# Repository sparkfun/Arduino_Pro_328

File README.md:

Arduino Pro 328
========================================

[*Arduino Pro 328 (DEV-10914)*](https://www.sparkfun.com/products/10914)

Arduino Pro does not come with connectors populated so that you can solder in any connector or wire with any orientation you need. 
We recommend first time Arduino users start with the Uno R3. It’s a great board that will get you up and running quickly. 
The Arduino Pro series is meant for users that understand the limitations of system voltage, lack of connectors, and USB off board.

Repository Contents
-------------------

* **/Hardware** - Eagle design files (.brd, .sch)
* **/Production** - Production panel files (.brd)

Documentation
--------------
* **[SparkFun Fritzing repo](https://github.com/sparkfun/Fritzing_Parts)** - Fritzing diagrams for SparkFun products.
* **[SparkFun 3D Model repo](https://github.com/sparkfun/3D_Models)** - 3D models of SparkFun products. 

Product Versions
----------------
* [3.3V/8MHz: DEV-10914](https://www.sparkfun.com/products/10914)- 3.3V/8MHz version of the Arduino Pro. 
* [5V/16MHz: DEV-10915] (https://www.sparkfun.com/products/10915)- 5V/16MHz version of the Arduino Pro. 

Revision History
----------------
Changes to v14 (date code: 8-24-11)
* updated library to increase annular ring size on all thru-hole pads (including package change on buzzer PTH)
* reposition 6x1 serial header to no longer overhang board
* BOM CHANGE - changes smd slide switch to stronger package with side mount tabs

Changes to v15 (date code: 9-21-11)
* changed package on the Buzzer to not include silk

Changes to v16 (date code: 12-20-11)
* Added OSHW logo

Changes to v17
* Added juicy silk graphics

Changes to v18
* Widened hard-to-read silk text

License Information
-------------------

This product is _**open source**_! 

Please review the LICENSE.md file for license information. 

If you have any questions or concerns on licensing, please contact techsupport@sparkfun.com.

Distributed as-is; no warranty is given.

- Your friends at SparkFun.

_**Note:** A portion of this sale is given back to Arduino LLC to help fund continued development of new tools and new IDE features._

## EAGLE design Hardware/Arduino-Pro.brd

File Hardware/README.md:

Arduino Pro Design Files
=====================================

The .sch and .brd files hare are Eagle CAD schematic and PCB design files from SparkFun Electronics.
A freeware version of Eagle can be found [here](http://www.cadsoftusa.com/download-eagle/freeware/).

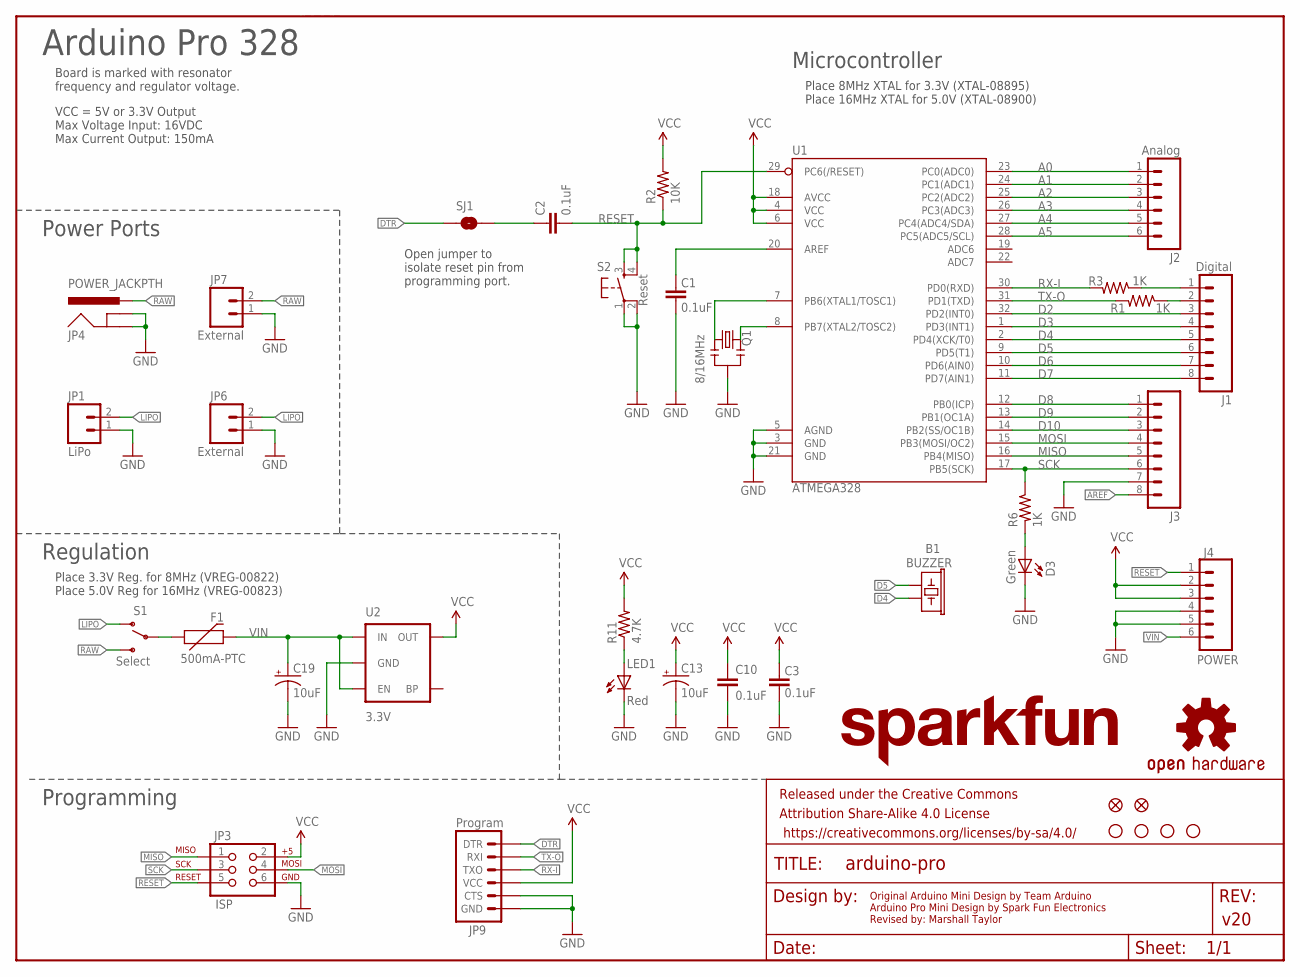
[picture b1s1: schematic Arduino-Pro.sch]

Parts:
B1: BUZZER; BUZZER-12MM-NS-KIT
C1, C2, C3, C10: 0.1uF; 0402-CAP
C13, C19: 10uF; EIA3216
D3: Green; LED-0603
F1: 500mA-PTC; PTC-1206
FRAME2: FRAME-LETTER; CREATIVE_COMMONS
J1: Digital; 1X08
J2: Analog; 1X06
J3: M081X08; 1X08
J4: POWER; 1X06
JP1: LiPo; JST-2-SMD
JP2, JP5: FIDUCIAL1X2.5; FIDUCIAL-1X2.5
JP3: ISP; 2X3
JP4: POWER_JACKPTH; POWER_JACK_PTH
JP6, JP7: External; 1X02
JP9: Program; 1X06-SMD
LED1: Red; LED-0603
Q1: 8/16MHz; RESONATOR-SMD
R1, R3, R6: 1K; 0402-RES
R2: 10K; 0402-RES
R11: 4.7K; 0402-RES
S1: Select; SWITCH-SPST-SMD-A
S2: Reset; TACTILE_SWITCH_SMD
SJ1: SOLDERJUMPERNC3; SJ_2S-NOTRACE
U1: ATMEGA328; TQFP32-08
U2: 3.3V; SOT23-5
U$1, U$3, U$9, U$10: STAND-OFF

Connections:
A0: J2.1, U1.23 (PC0(ADC0))
A1: J2.2, U1.24 (PC1(ADC1))
A2: J2.3, U1.25 (PC2(ADC2))
A3: J2.4, U1.26 (PC3(ADC3))
A4: J2.5, U1.27 (PC4(ADC4/SDA))
A5: J2.6, U1.28 (PC5(ADC5/SCL))
AREF: C1.2, J3.8, U1.20 (AREF)
D2: J1.3, U1.32 (PD2(INT0))
D3: J1.4, U1.1 (PD3(INT1))
D4: B1.- (2), J1.5, U1.2 (PD4(XCK/T0))
D5: B1.+ (1), J1.6, U1.9 (PD5(T1))
D6: J1.7, U1.10 (PD6(AIN0))
D7: J1.8, U1.11 (PD7(AIN1))
D8: J3.1, U1.12 (PB0(ICP))
D9: J3.2, U1.13 (PB1(OC1A))
D10: J3.3, U1.14 (PB2(SS/OC1B))
DTR: JP9.1 (DTR), SJ1.1
GND: C1.1, C3.1, C10.2, C13.C (-), C19.C (-), D3.C, J3.7, J4.4, J4.5, JP1.1, JP3.6, JP4.GND, JP4.GNDBREAK, JP6.1, JP7.1, JP9.5 (CTS), JP9.6 (GND), LED1.C, Q1.2, S2.1, S2.2, U1.3 (GND), U1.5 (AGND), U1.21 (GND), U2.2 (GND)
LIPO: JP1.2, JP6.2, S1.1 (O)
MISO: J3.5, JP3.1, U1.16 (PB4(MISO))
MOSI: J3.4, JP3.4, U1.15 (PB3(MOSI/OC2))
unnamed: C2.1, SJ1.2
unnamed: Q1.1, U1.8 (PB7(XTAL2/TOSC2))
unnamed: Q1.3, U1.7 (PB6(XTAL1/TOSC1))
unnamed: D3.A, R6.2
unnamed: F1.1, S1.2
unnamed: LED1.A, R11.1
RAW: JP4.PWR, JP7.2, S1.3 (S)
RESET: C2.2, J4.1, JP3.5, R2.1, S2.3, S2.4, U1.29 (PC6(/RESET))
RX-I: JP9.3 (TXO), R3.2, U1.30 (PD0(RXD))
RX-IP: J1.2, R1.1
SCK: J3.6, JP3.3, R6.1, U1.17 (PB5(SCK))
TX-O: JP9.2 (RXI), R1.2, U1.31 (PD1(TXD))
TX-OP: J1.1, R3.1
VCC: C3.2, C10.1, C13.A (+), J4.2, J4.3, JP3.2, JP9.4 (VCC), R2.2, R11.2, U1.4 (VCC), U1.6 (VCC), U1.18 (AVCC), U2.5 (OUT)
VIN: C19.A (+), F1.2, J4.6, U2.1 (IN), U2.3 (EN)

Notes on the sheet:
VCC = 5V or 3.3V Output Max Voltage Input: 16VDC Max Current Output: 150mA
Board is marked with resonator frequency and regulator voltage.
v20
Original Arduino Mini Design by Team Arduino Arduino Pro Mini Design by Spark Fun Electronics Revised by: Marshall Taylor
Power Ports
Regulation
Programming
Microcontroller
Arduino Pro 328
Open jumper to isolate reset pin from programming port.
Place 8MHz XTAL for 3.3V (XTAL-08895) Place 16MHz XTAL for 5.0V (XTAL-08900)
Place 3.3V Reg. for 8MHz (VREG-00822) Place 5.0V Reg for 16MHz (VREG-00823)

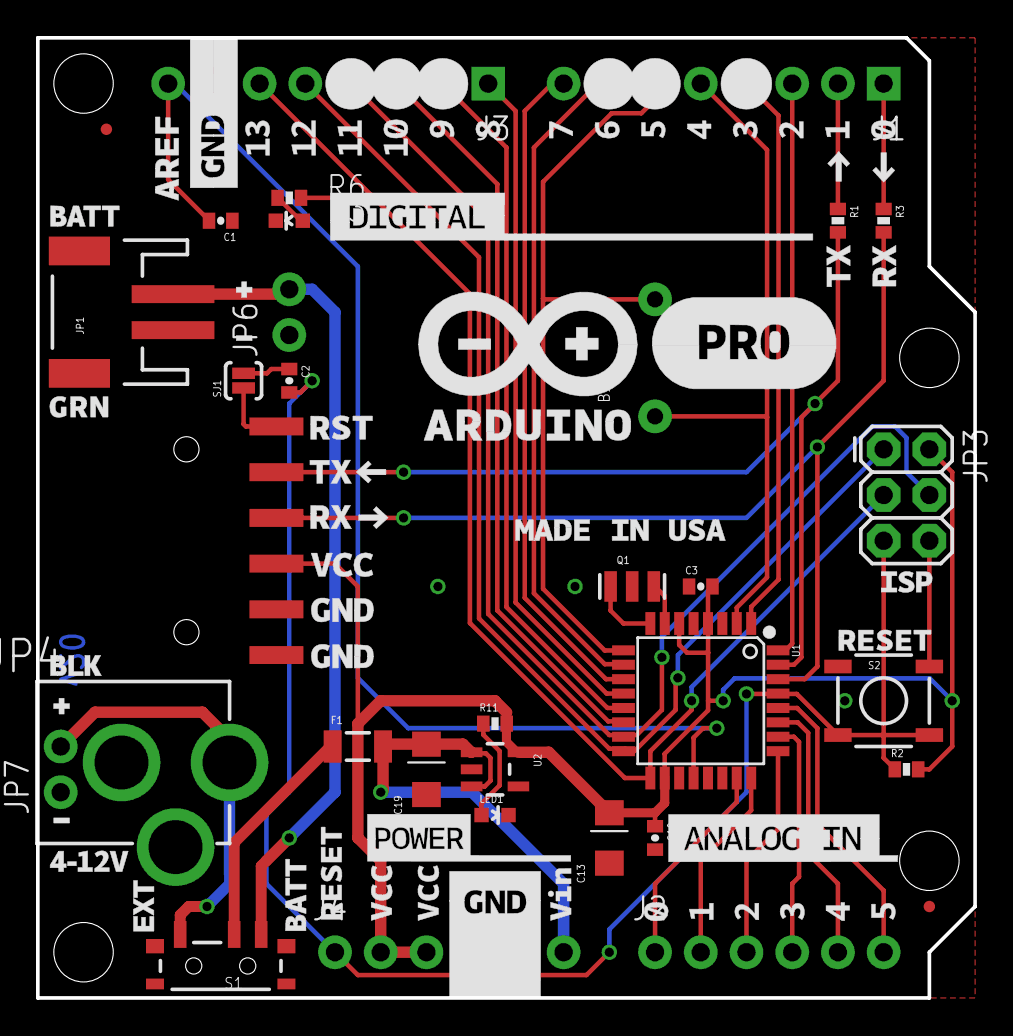
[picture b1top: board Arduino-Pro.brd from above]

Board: 2 copper layers, 52.1 x 53.3 mm, 38 parts (0 on the bottom side), 36 nets.

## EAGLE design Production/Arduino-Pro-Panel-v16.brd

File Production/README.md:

SparkFun Arduino Pro Production Files
=========================================

These are the production files SparkFun uses for printing PCBs.

License Information
-------------------
This product is open source! 

The hardware is released under [Creative Commons ShareAlike 4.0 International](https://creativecommons.org/licenses/by-sa/4.0/).

Please use, reuse, and modify these files as you see fit. Please maintain attribution to SparkFun Electronics and release anything derivative under the same license.

Distributed as-is; no warranty is given.

- Your friends at SparkFun.

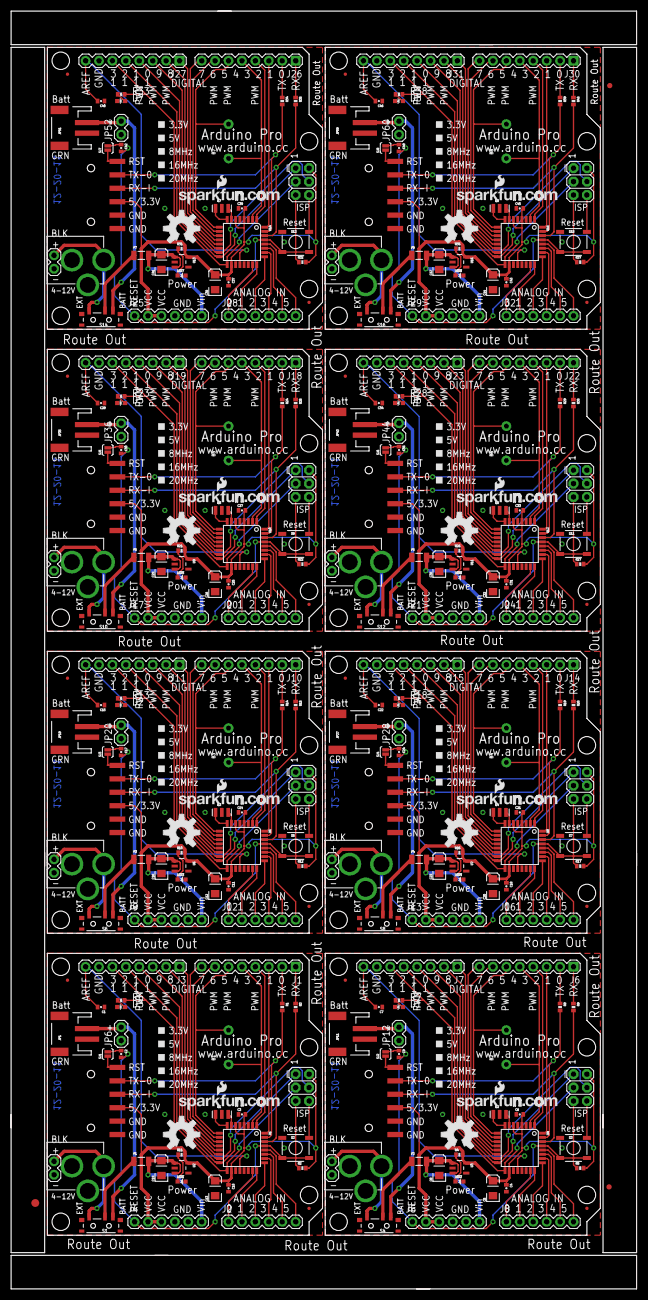
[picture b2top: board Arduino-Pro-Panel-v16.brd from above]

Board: 2 copper layers, 118.4 x 241.8 mm, 315 parts (0 on the bottom side), 288 nets.

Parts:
B1, B2, B3, B4, B5, B6, B7, B8: BUZZER; BUZZER-12MM-NS-KIT
C1, C2, C3, C4, C6, C7, C9, C10, C11, C14, C15, C17, C18, C21, C22, C24, C25, C27, C28, C30, C31, C33, C34, C36, C37, C39, C40, C42, C43, C45, C46, C48: 0.1uF; 0402-CAP
C5, C8, C12, C13, C16, C19, C20, C23, C26, C29, C32, C35, C38, C41, C44, C47: 10uF; EIA3216
D1, D2, D3, D4, D5, D6, D7, D8: Green; LED-0603
E$1: FIDUCIAL-1.5X3
E$5, E$7: FIDUCIAL-1X2
F1, F2, F3, F4, F5, F6, F7, F8: 500mA-PTC; PTC-1206
J1, J6, J10, J14, J18, J22, J26, J30: Digital; 1X08
J2, J8, J12, J16, J20, J24, J28, J32: Analog; 1X06
J3, J7, J11, J15, J19, J23, J27, J31: 1X08
J4, J5, J9, J13, J17, J21, J25, J29: POWER; 1X06
JP1, JP11, JP19, JP27, JP35, JP43, JP51, JP59: LiPo; JST-2-SMD
JP2, JP5, JP15, JP16, JP23, JP24, JP31, JP32, JP39, JP40, JP47, JP48, JP55, JP56, JP63, JP64: FIDUCIAL1X2.5; FIDUCIAL-1X2.5
JP3, JP10, JP18, JP26, JP34, JP42, JP50, JP58: ISP; 2X3
JP4, JP8, JP17, JP25, JP33, JP41, JP49, JP57: POWER_JACKPTH; POWER_JACK_PTH
JP6, JP7, JP12, JP13, JP20, JP21, JP28, JP29, JP36, JP37, JP44, JP45, JP52, JP53, JP60, JP61: External; 1X02
JP9, JP14, JP22, JP30, JP38, JP46, JP54, JP62: Program; 1X06-SMD
LED1, LED2, LED3, LED4, LED5, LED6, LED7, LED8: Red; LED-0603
Q1, Q2, Q3, Q4, Q5, Q6, Q7, Q8: RESONATORSMD; RESONATOR-SMD
R1, R3, R6, R7, R8, R9, R13, R14, R15, R18, R19, R20, R23, R24, R25, R28, R29, R30, R33, R34, R35, R38, R39, R40: 1K; 0402-RES
R2, R5, R12, R17, R22, R27, R32, R37: 10K; 0402-RES
R4, R10, R11, R16, R21, R26, R31, R36: 4.7K; 0402-RES
S1, S4, S6, S8, S10, S12, S14, S16: Select; SWITCH-SPST-SMD-A
S2, S3, S5, S7, S9, S11, S13, S15: Reset; TACTILE_SWITCH_SMD
SJ1, SJ2, SJ3, SJ4, SJ5, SJ6, SJ7, SJ8: SOLDERJUMPERNC3; SJ_2S-NOTRACE
U1, U4, U6, U8, U10, U12, U14, U16: ATMEGA328; TQFP32-08
U2, U3, U5, U7, U9, U11, U13, U15: 3.3V; SOT23-5
U$1, U$3, U$4, U$5, U$7, U$8, U$9, U$10, U$13, U$14, U$16, U$17, U$19, U$20, U$22, U$23, U$25, U$26, U$28, U$29, U$31, U$32, U$34, U$35, U$37, U$38, U$40, U$41, U$43, U$44, U$46, U$47: STAND-OFF
U$2, U$12, U$18, U$24, U$30, U$36, U$42, U$48: OSHW-LOGOL; OSHW-LOGO-L
U$6, U$11, U$15, U$21, U$27, U$33, U$39, U$45: LOGO-SFENEW; SFE-NEW-WEBLOGO

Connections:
A0: J2.1, U1.23
A1: J2.2, U1.24
A2: J2.3, U1.25
A3: J2.4, U1.26
A4: J2.5, U1.27
A5: J2.6, U1.28
A6: J8.6, U4.28
A7: J8.5, U4.27
A8: J8.4, U4.26
A9: J8.3, U4.25
A10: J8.2, U4.24
A11: J8.1, U4.23
A12: J12.6, U6.28
A13: J12.5, U6.27
A14: J12.4, U6.26
A15: J12.3, U6.25
A16: J12.2, U6.24
A17: J12.1, U6.23
A18: J16.6, U8.28
A19: J16.5, U8.27
A20: J16.4, U8.26
A21: J16.3, U8.25
A22: J16.2, U8.24
A23: J16.1, U8.23
A24: J20.6, U10.28
A25: J20.5, U10.27
A26: J20.4, U10.26
A27: J20.3, U10.25
A28: J20.2, U10.24
A29: J20.1, U10.23
A30: J24.6, U12.28
A31: J24.5, U12.27
A32: J24.4, U12.26
A33: J24.3, U12.25
A34: J24.2, U12.24
A35: J24.1, U12.23
A36: J28.6, U14.28
A37: J28.5, U14.27
A38: J28.4, U14.26
A39: J28.3, U14.25
A40: J28.2, U14.24
A41: J28.1, U14.23
A42: J32.6, U16.28
A43: J32.5, U16.27
A44: J32.4, U16.26
A45: J32.3, U16.25
A46: J32.2, U16.24
A47: J32.1, U16.23
AREF: C1.2, J3.8, U1.20
AREF1: C7.2, J7.8, U4.20
AREF2: C15.2, J11.8, U6.20
AREF3: C22.2, J15.8, U8.20
AREF4: C28.2, J19.8, U10.20
AREF5: C34.2, J23.8, U12.20
AREF6: C40.2, J27.8, U14.20
AREF7: C46.2, J31.8, U16.20
D1: J7.3, U4.14
D2: J1.3, U1.32
D3: J1.4, U1.1
D4: B1.-, J1.5, U1.2
D5: B1.+, J1.6, U1.9
D6: J1.7, U1.10
D7: J1.8, U1.11
D8: J3.1, U1.12
D9: J3.2, U1.13
D10: J3.3, U1.14
D11: J7.2, U4.13
D12: J7.1, U4.12
D13: J6.8, U4.11
D14: J6.7, U4.10
D15: B2.+, J6.6, U4.9
D16: B2.-, J6.5, U4.2
D17: J6.4, U4.1
D18: J6.3, U4.32
D19: J11.3, U6.14
D20: J11.2, U6.13
D21: J11.1, U6.12
D22: J10.8, U6.11
D23: J10.7, U6.10
D24: B3.+, J10.6, U6.9
D25: B3.-, J10.5, U6.2
D26: J10.4, U6.1
D27: J10.3, U6.32
D28: J15.3, U8.14
D29: J15.2, U8.13
D30: J15.1, U8.12
D31: J14.8, U8.11
D32: J14.7, U8.10
D33: B4.+, J14.6, U8.9
D34: B4.-, J14.5, U8.2
D35: J14.4, U8.1
D36: J14.3, U8.32
D37: J19.3, U10.14
D38: J19.2, U10.13
D39: J19.1, U10.12
D40: J18.8, U10.11
D41: J18.7, U10.10
D42: B5.+, J18.6, U10.9
D43: B5.-, J18.5, U10.2
D44: J18.4, U10.1
D45: J18.3, U10.32
D46: J23.3, U12.14
D47: J23.2, U12.13
D48: J23.1, U12.12
D49: J22.8, U12.11
D50: J22.7, U12.10
D51: B6.+, J22.6, U12.9
D52: B6.-, J22.5, U12.2
D53: J22.4, U12.1
D54: J22.3, U12.32
D55: J27.3, U14.14
D56: J27.2, U14.13
D57: J27.1, U14.12
D58: J26.8, U14.11
D59: J26.7, U14.10
D60: B7.+, J26.6, U14.9
D61: B7.-, J26.5, U14.2
D62: J26.4, U14.1
D63: J26.3, U14.32
D64: J31.3, U16.14
D65: J31.2, U16.13
D66: J31.1, U16.12
D67: J30.8, U16.11
D68: J30.7, U16.10
D69: B8.+, J30.6, U16.9
D70: B8.-, J30.5, U16.2
D71: J30.4, U16.1
D72: J30.3, U16.32
DTR: JP9.1, SJ1.1
DTR1: JP14.1, SJ2.1
DTR2: JP22.1, SJ3.1
DTR3: JP30.1, SJ4.1
DTR4: JP38.1, SJ5.1
DTR5: JP46.1, SJ6.1
DTR6: JP54.1, SJ7.1
DTR7: JP62.1, SJ8.1
GND: C1.1, C3.1, C10.2, C13.C, C19.C, D3.C, J3.7, J4.4, J4.5, JP1.1, JP3.6, JP4.GND, JP4.GNDBREAK, JP6.1, JP7.1, JP9.5, JP9.6, LED1.C, Q1.2, S2.1, S2.2, U1.3, U1.5, U1.21, U2.2
GND1: C4.2, C5.C, C6.1, C7.1, C8.C, D1.C, J5.4, J5.5, J7.7, JP8.GND, JP8.GNDBREAK, JP10.6, JP11.1, JP12.1, JP13.1, JP14.5, JP14.6, LED2.C, Q2.2, S3.1, S3.2, U3.2, U4.3, U4.5, U4.21
GND2: C11.2, C12.C, C14.1, C15.1, C16.C, D2.C, J9.4, J9.5, J11.7, JP17.GND, JP17.GNDBREAK, JP18.6, JP19.1, JP20.1, JP21.1, JP22.5, JP22.6, LED3.C, Q3.2, S5.1, S5.2, U5.2, U6.3, U6.5, U6.21
GND3: C18.2, C20.C, C21.1, C22.1, C23.C, D4.C, J13.4, J13.5, J15.7, JP25.GND, JP25.GNDBREAK, JP26.6, JP27.1, JP28.1, JP29.1, JP30.5, JP30.6, LED4.C, Q4.2, S7.1, S7.2, U7.2, U8.3, U8.5, U8.21
GND4: C25.2, C26.C, C27.1, C28.1, C29.C, D5.C, J17.4, J17.5, J19.7, JP33.GND, JP33.GNDBREAK, JP34.6, JP35.1, JP36.1, JP37.1, JP38.5, JP38.6, LED5.C, Q5.2, S9.1, S9.2, U9.2, U10.3, U10.5, U10.21
GND5: C31.2, C32.C, C33.1, C34.1, C35.C, D6.C, J21.4, J21.5, J23.7, JP41.GND, JP41.GNDBREAK, JP42.6, JP43.1, JP44.1, JP45.1, JP46.5, JP46.6, LED6.C, Q6.2, S11.1, S11.2, U11.2, U12.3, U12.5, U12.21
GND6: C37.2, C38.C, C39.1, C40.1, C41.C, D7.C, J25.4, J25.5, J27.7, JP49.GND, JP49.GNDBREAK, JP50.6, JP51.1, JP52.1, JP53.1, JP54.5, JP54.6, LED7.C, Q7.2, S13.1, S13.2, U13.2, U14.3, U14.5, U14.21
GND7: C43.2, C44.C, C45.1, C46.1, C47.C, D8.C, J29.4, J29.5, J31.7, JP57.GND, JP57.GNDBREAK, JP58.6, JP59.1, JP60.1, JP61.1, JP62.5, JP62.6, LED8.C, Q8.2, S15.1, S15.2, U15.2, U16.3, U16.5, U16.21
LIPO: JP1.2, JP6.2, S1.1
LIPO1: JP11.2, JP12.2, S4.1
LIPO2: JP19.2, JP20.2, S6.1
LIPO3: JP27.2, JP28.2, S8.1
LIPO4: JP35.2, JP36.2, S10.1
LIPO5: JP43.2, JP44.2, S12.1
LIPO6: JP51.2, JP52.2, S14.1
LIPO7: JP59.2, JP60.2, S16.1
MISO: J3.5, JP3.1, U1.16
MISO1: J7.5, JP10.1, U4.16
MISO2: J11.5, JP18.1, U6.16
MISO3: J15.5, JP26.1, U8.16
MISO4: J19.5, JP34.1, U10.16
MISO5: J23.5, JP42.1, U12.16
MISO6: J27.5, JP50.1, U14.16
MISO7: J31.5, JP58.1, U16.16
MOSI: J3.4, JP3.4, U1.15
MOSI1: J7.4, JP10.4, U4.15
MOSI2: J11.4, JP18.4, U6.15
MOSI3: J15.4, JP26.4, U8.15
MOSI4: J19.4, JP34.4, U10.15
MOSI5: J23.4, JP42.4, U12.15
MOSI6: J27.4, JP50.4, U14.15
MOSI7: J31.4, JP58.4, U16.15
unnamed: C2.1, SJ1.2
unnamed: LED2.A, R4.1
unnamed: Q1.1, U1.8
unnamed: Q1.3, U1.7
unnamed: D1.A, R7.2
unnamed: F2.1, S4.2
unnamed: D3.A, R6.2
unnamed: Q2.1, U4.8
unnamed: Q2.3, U4.7
unnamed: C9.1, SJ2.2
unnamed: LED3.A, R10.1
unnamed: D2.A, R13.2
unnamed: F3.1, S6.2
unnamed: Q3.1, U6.8
unnamed: Q3.3, U6.7
unnamed: C17.1, SJ3.2
unnamed: LED4.A, R16.1
unnamed: D4.A, R18.2
unnamed: F4.1, S8.2
unnamed: Q4.1, U8.8
unnamed: Q4.3, U8.7
unnamed: C24.1, SJ4.2
unnamed: LED5.A, R21.1
unnamed: D5.A, R23.2
unnamed: F1.1, S1.2
unnamed: F5.1, S10.2
unnamed: Q5.1, U10.8
unnamed: Q5.3, U10.7
unnamed: C30.1, SJ5.2
unnamed: LED6.A, R26.1
unnamed: D6.A, R28.2
unnamed: F6.1, S12.2
unnamed: Q6.1, U12.8
unnamed: Q6.3, U12.7
unnamed: C36.1, SJ6.2
unnamed: LED7.A, R31.1
unnamed: D7.A, R33.2
unnamed: LED1.A, R11.1
unnamed: F7.1, S14.2
unnamed: Q7.1, U14.8
unnamed: Q7.3, U14.7
unnamed: C42.1, SJ7.2
unnamed: LED8.A, R36.1
unnamed: D8.A, R38.2
unnamed: F8.1, S16.2
unnamed: Q8.1, U16.8
unnamed: Q8.3, U16.7
unnamed: C48.1, SJ8.2
RAW: JP4.PWR, JP7.2, S1.3
RAW1: JP8.PWR, JP13.2, S4.3
RAW2: JP17.PWR, JP21.2, S6.3
RAW3: JP25.PWR, JP29.2, S8.3
RAW4: JP33.PWR, JP37.2, S10.3
RAW5: JP41.PWR, JP45.2, S12.3
RAW6: JP49.PWR, JP53.2, S14.3
RAW7: JP57.PWR, JP61.2, S16.3
RESET: C2.2, J4.1, JP3.5, R2.1, S2.3, S2.4, U1.29
RESET1: C9.2, J5.1, JP10.5, R5.1, S3.3, S3.4, U4.29
RESET2: C17.2, J9.1, JP18.5, R12.1, S5.3, S5.4, U6.29
RESET3: C24.2, J13.1, JP26.5, R17.1, S7.3, S7.4, U8.29
RESET4: C30.2, J17.1, JP34.5, R22.1, S9.3, S9.4, U10.29
RESET5: C36.2, J21.1, JP42.5, R27.1, S11.3, S11.4, U12.29
RESET6: C42.2, J25.1, JP50.5, R32.1, S13.3, S13.4, U14.29
RESET7: C48.2, J29.1, JP58.5, R37.1, S15.3, S15.4, U16.29
RX-I: JP9.3, R3.2, U1.30
RX-I1: JP14.3, R9.2, U4.30
RX-I2: JP22.3, R15.2, U6.30
RX-I3: JP30.3, R20.2, U8.30
RX-I4: JP38.3, R25.2, U10.30
RX-I5: JP46.3, R30.2, U12.30
RX-I6: JP54.3, R35.2, U14.30
RX-I7: JP62.3, R40.2, U16.30
RX-IP: J1.2, R1.1
RX-IP1: J6.2, R8.1
RX-IP2: J10.2, R14.1
RX-IP3: J14.2, R19.1
RX-IP4: J18.2, R24.1
RX-IP5: J22.2, R29.1
RX-IP6: J26.2, R34.1
RX-IP7: J30.2, R39.1
SCK: J3.6, JP3.3, R6.1, U1.17
SCK1: J7.6, JP10.3, R7.1, U4.17
SCK2: J11.6, JP18.3, R13.1, U6.17
SCK3: J15.6, JP26.3, R18.1, U8.17
SCK4: J19.6, JP34.3, R23.1, U10.17
SCK5: J23.6, JP42.3, R28.1, U12.17
SCK6: J27.6, JP50.3, R33.1, U14.17
SCK7: J31.6, JP58.3, R38.1, U16.17
TX-O: JP9.2, R1.2, U1.31
TX-O1: JP14.2, R8.2, U4.31
TX-O2: JP22.2, R14.2, U6.31
TX-O3: JP30.2, R19.2, U8.31
TX-O4: JP38.2, R24.2, U10.31
TX-O5: JP46.2, R29.2, U12.31
TX-O6: JP54.2, R34.2, U14.31
TX-O7: JP62.2, R39.2, U16.31
TX-OP: J1.1, R3.1
TX-OP1: J6.1, R9.1
TX-OP2: J10.1, R15.1
TX-OP3: J14.1, R20.1
TX-OP4: J18.1, R25.1
TX-OP5: J22.1, R30.1
TX-OP6: J26.1, R35.1
TX-OP7: J30.1, R40.1
VCC: C3.2, C10.1, C13.A, J4.2, J4.3, JP3.2, JP9.4, R2.2, R11.2, U1.4, U1.6, U1.18, U2.5
VCC1: C4.1, C5.A, C6.2, J5.2, J5.3, JP10.2, JP14.4, R4.2, R5.2, U3.5, U4.4, U4.6, U4.18
VCC2: C11.1, C12.A, C14.2, J9.2, J9.3, JP18.2, JP22.4, R10.2, R12.2, U5.5, U6.4, U6.6, U6.18
VCC3: C18.1, C20.A, C21.2, J13.2, J13.3, JP26.2, JP30.4, R16.2, R17.2, U7.5, U8.4, U8.6, U8.18
VCC4: C25.1, C26.A, C27.2, J17.2, J17.3, JP34.2, JP38.4, R21.2, R22.2, U9.5, U10.4, U10.6, U10.18
VCC5: C31.1, C32.A, C33.2, J21.2, J21.3, JP42.2, JP46.4, R26.2, R27.2, U11.5, U12.4, U12.6, U12.18
VCC6: C37.1, C38.A, C39.2, J25.2, J25.3, JP50.2, JP54.4, R31.2, R32.2, U13.5, U14.4, U14.6, U14.18
VCC7: C43.1, C44.A, C45.2, J29.2, J29.3, JP58.2, JP62.4, R36.2, R37.2, U15.5, U16.4, U16.6, U16.18
VIN: C19.A, F1.2, J4.6, U2.1, U2.3
VIN1: C8.A, F2.2, J5.6, U3.1, U3.3
VIN2: C16.A, F3.2, J9.6, U5.1, U5.3
VIN3: C23.A, F4.2, J13.6, U7.1, U7.3
VIN4: C29.A, F5.2, J17.6, U9.1, U9.3
VIN5: C35.A, F6.2, J21.6, U11.1, U11.3
VIN6: C41.A, F7.2, J25.6, U13.1, U13.3
VIN7: C47.A, F8.2, J29.6, U15.1, U15.3

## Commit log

2015-11-11 Adding files, updating README
2015-11-11 Adding v16 files from Kentro
2015-11-11 Update README.md
    Adding collaboration info
2015-11-18 created new panel
2016-07-18 Added test-silk board design and alternate libraries
2016-07-18 Converted to 0.001 width
2016-07-20 Refined silk application
2016-07-21 Finished design review and checklist
2016-08-02 Updated schematic to standard, moved rev info to readme
2016-08-11 Fixed schematic issues
2016-08-12 Fixed more schematic issues
2016-08-15 Re-imported silk graphics, removed two-pin silk outlines, incremented rev number to 1.8
2016-08-15 Post review and checklist verification
2016-08-17 Added dual-part SKU information in schematic
2016-09-13 Enlarged circles, incremented version number
2016-09-15 Increased zero widths and expanded ordering instructions

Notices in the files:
parts and their libraries:
SparkFun-Aesthetics: Licensing: Creative Commons ShareAlike 4.0 International - https://creativecommons.org/licenses/by-sa/4.0
SparkFun-Aesthetics: Released under the Creative Commons Attribution Share-Alike 4.0 License
SparkFun-Aesthetics: Released under the Creative Commons
